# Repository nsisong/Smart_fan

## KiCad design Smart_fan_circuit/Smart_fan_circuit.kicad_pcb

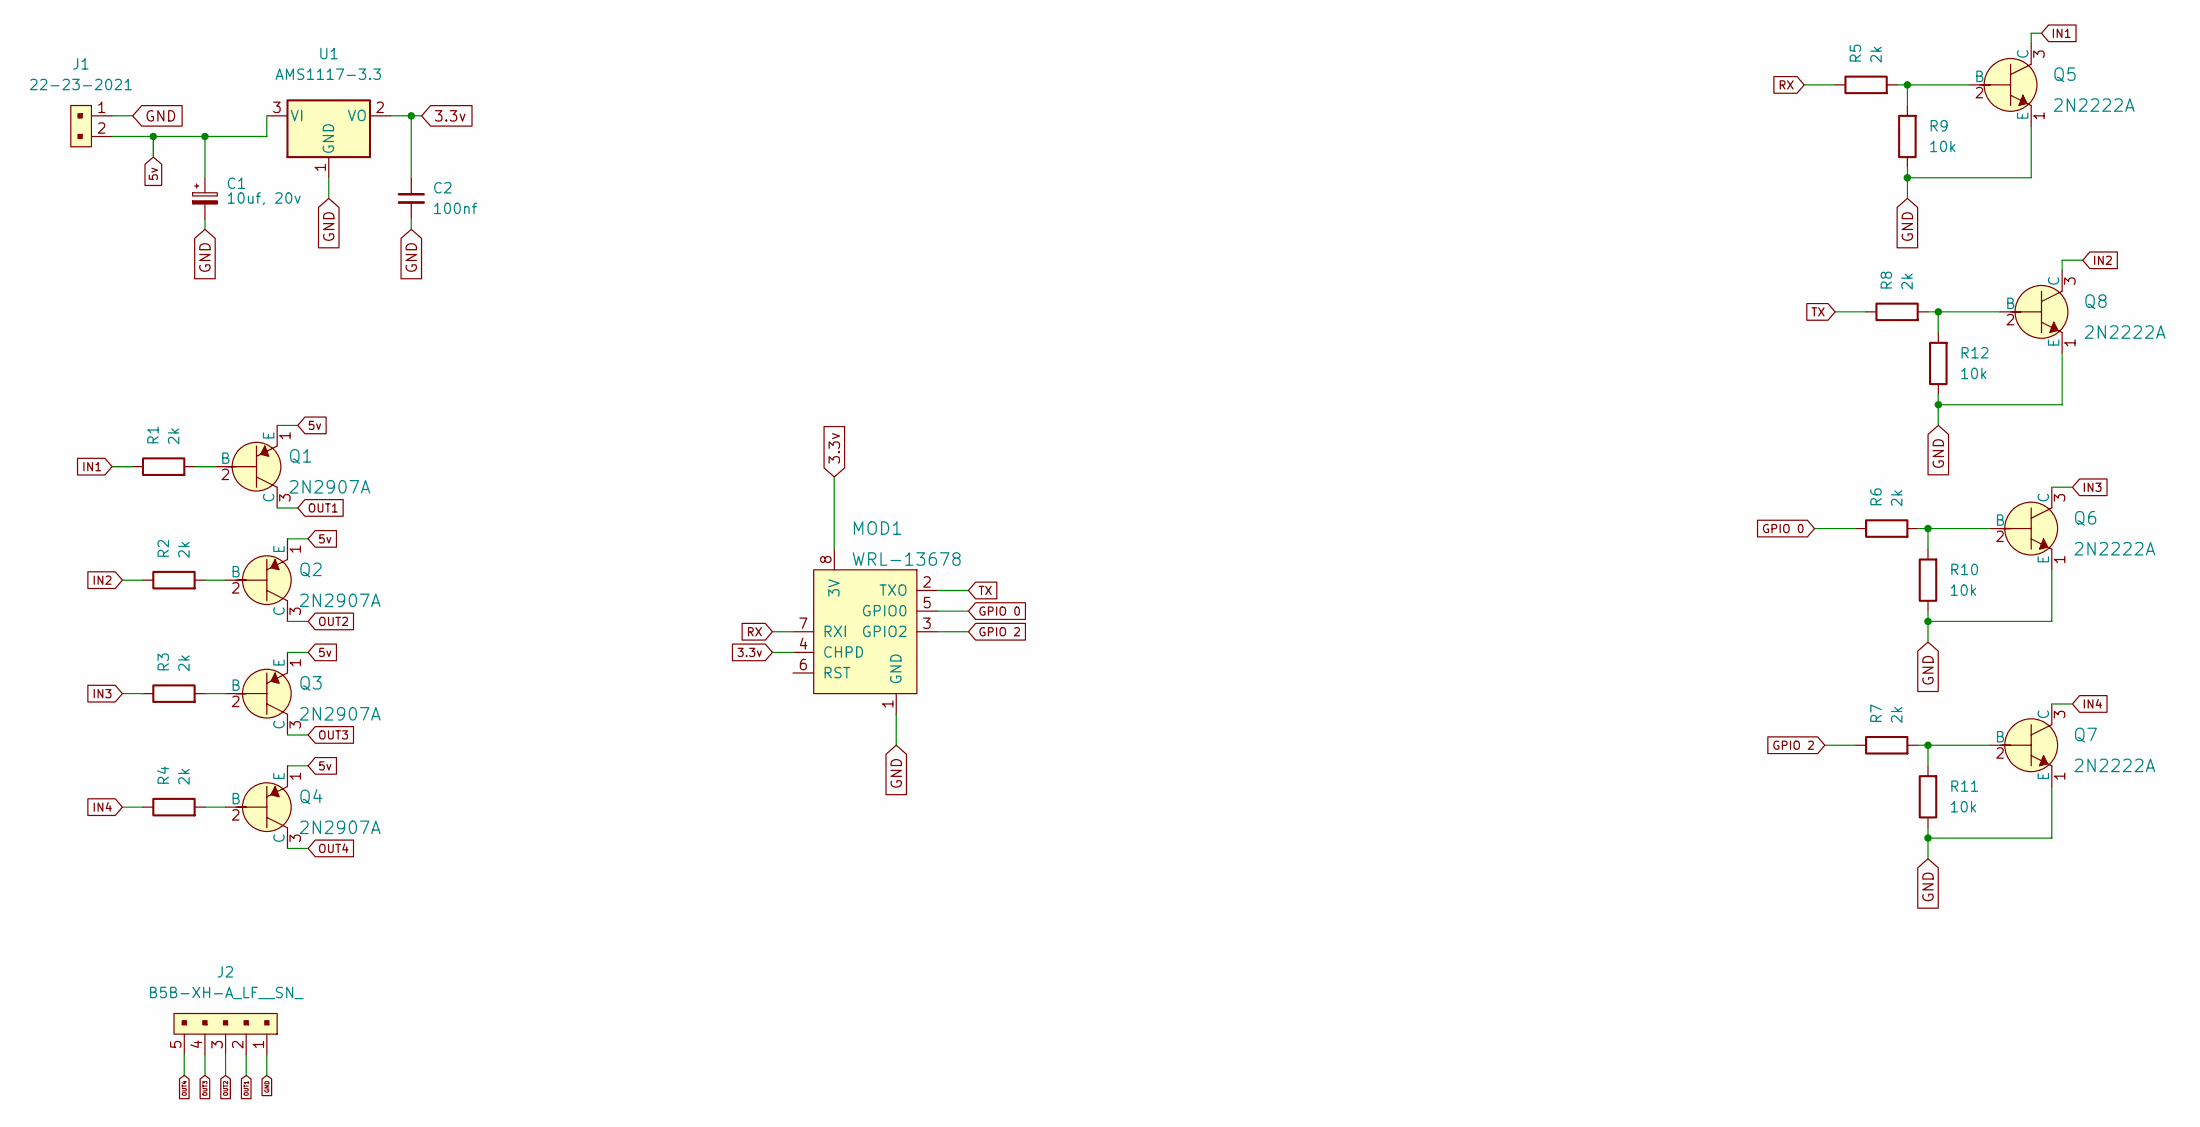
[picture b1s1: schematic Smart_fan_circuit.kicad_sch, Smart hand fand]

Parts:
C1: 10uf, 20v
C2: 100nf
J1: 22-23-2021; PinHeader_1x2_P2.54mm_Drill1.02mm; MPN 22-23-2021; Digi-Key_PN WM4200-ND
J2: B5B-XH-A_LF__SN_; PinHeader_1x5_P2.5mm_Drill1.1mm; MPN B5B-XH-A(LF)(SN); Digi-Key_PN 455-2270-ND
MOD1: WRL-13678; Wifi_Module_ESP8266_WRL-13678; MPN WRL-13678; Digi-Key_PN 1568-1235-ND
Q1, Q2, Q3, Q4: 2N2907A; MPN 2N2907A; Digi-Key_PN 2N2907ACS-ND
Q5, Q6, Q7, Q8: 2N2222A; MPN 2N2222A; Digi-Key_PN 2N2222ACS-ND
R1, R2, R3, R4, R5, R6, R7, R8: 2k
R9, R10, R11, R12: 10k
U1: AMS1117-3.3

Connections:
3.3v: C2.1, MOD1.4 (CHPD), MOD1.8 (3V), U1.2 (VO)
5v: C1.1, J1.2, Q1.1 (E), Q2.1 (E), Q3.1 (E), Q4.1 (E), U1.3 (VI)
GND: C1.2, C2.2, J1.1, J2.1, MOD1.1 (GND), Q5.1 (E), Q6.1 (E), Q7.1 (E), Q8.1 (E), R9.1, R10.1, R11.1, R12.1, U1.1 (GND)
GPIO 0: MOD1.5 (GPIO0), R6.1
GPIO 2: MOD1.3 (GPIO2), R7.1
IN1: Q5.3 (C), R1.1
IN2: Q8.3 (C), R2.1
IN3: Q6.3 (C), R3.1
IN4: Q7.3 (C), R4.1
unnamed: Q1.2 (B), R1.2
unnamed: Q2.2 (B), R2.2
unnamed: Q3.2 (B), R3.2
unnamed: Q4.2 (B), R4.2
unnamed: Q5.2 (B), R5.2, R9.2
unnamed: Q6.2 (B), R6.2, R10.2
unnamed: Q7.2 (B), R7.2, R11.2
unnamed: Q8.2 (B), R8.2, R12.2
OUT1: J2.2, Q1.3 (C)
OUT2: J2.3, Q2.3 (C)
OUT3: J2.4, Q3.3 (C)
OUT4: J2.5, Q4.3 (C)
RX: MOD1.7 (RXI), R5.1
TX: MOD1.2 (TXO), R8.1

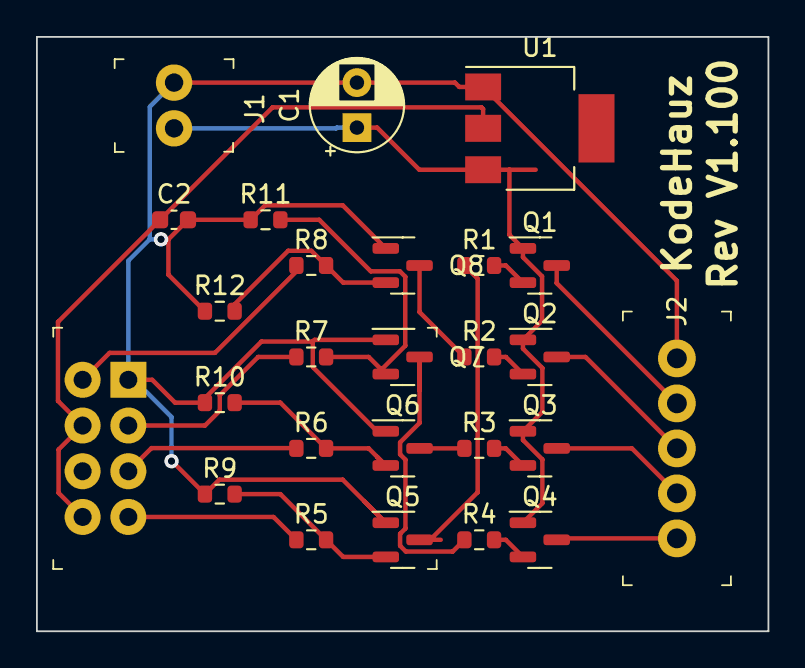
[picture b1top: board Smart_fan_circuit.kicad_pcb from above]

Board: 2 copper layers, 40.6 x 33.0 mm, 26 parts (0 on the bottom side), 23 nets.

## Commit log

2022-05-05 adding components to the circuit
2022-05-09 started working on BMS v1.101
2022-05-10 completed the fan circuit
